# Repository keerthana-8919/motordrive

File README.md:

[L293D_Motor_Driver_Project_Report.docx](https://github.com/user-attachments/files/25310511/L293D_Motor_Driver_Project_Report.docx)

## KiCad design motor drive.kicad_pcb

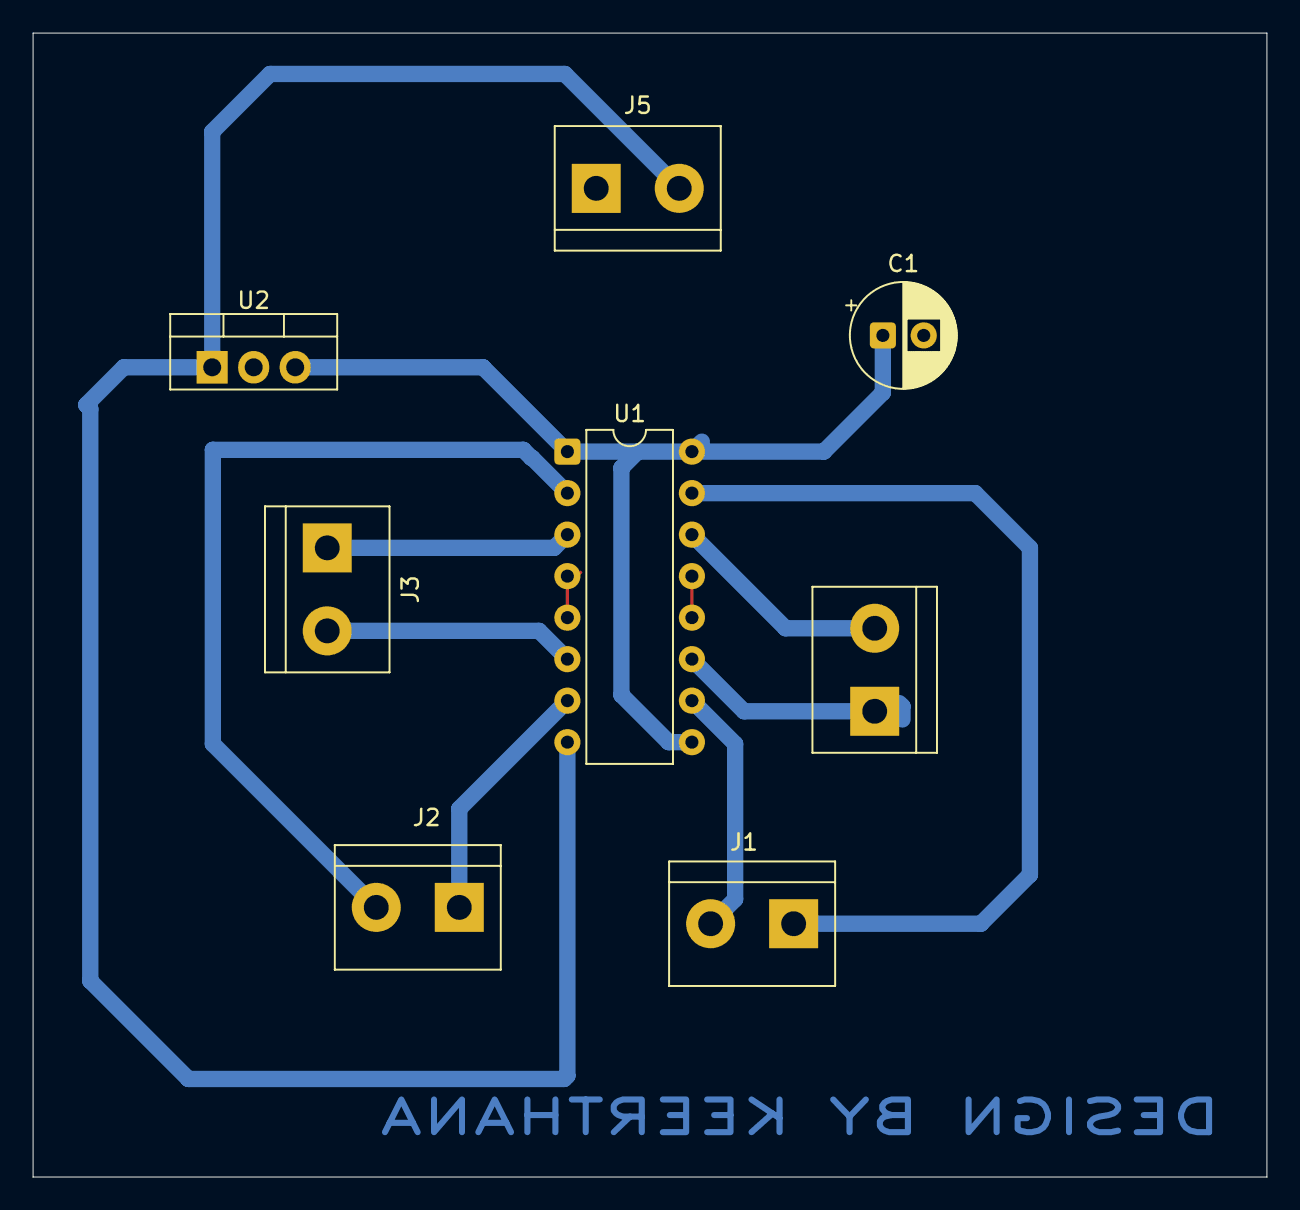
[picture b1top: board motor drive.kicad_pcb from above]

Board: 2 copper layers, 75.5 x 70.0 mm, 8 parts (0 on the bottom side), 11 nets.

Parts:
C1: C; CP_Radial_D6.3mm_P2.50mm
J1, J2, J3, J4, J5: Screw_Terminal_01x02; TerminalBlock_bornier-2_P5.08mm
U1: L293D; DIP-16_W7.62mm
U2: L7805; TO-220-3_Vertical

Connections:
GND: C1.2, J5.1, U1.4 (GND), U1.5 (GND), U1.12 (GND), U1.13 (GND), U2.2 (GND)
unnamed: J1.1, U1.15 (4A)
unnamed: J1.2, U1.10 (3A)
unnamed: J2.1, U1.7 (2A)
unnamed: J2.2, U1.2 (1A)
unnamed: J3.1, U1.3 (1Y)
unnamed: J3.2, U1.6 (2Y)
unnamed: J4.1, U1.11 (3Y)
unnamed: J4.2, U1.14 (4Y)
unnamed: J5.2, U1.8 (VCC2), U2.1 (IN)
unnamed: C1.1, U1.1 (EN1,2), U1.9 (EN3,4), U1.16 (VCC1), U2.3 (OUT)

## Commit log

2026-02-14 Add link to L293D Motor Driver project report
2026-02-14 Update link to L293D Motor Driver Project Report
